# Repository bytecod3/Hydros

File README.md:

### Introduction
Hydros

### Enabling floating point on MicroChip Studio 7
Refer to this article:
https://startingelectronics.org/articles/atmel-AVR-8-bit/print-float-atmel-studio-7/

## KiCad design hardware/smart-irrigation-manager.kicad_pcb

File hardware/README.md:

# smart-irrigation-manager

## Getting started

To make it easy for you to get started with GitLab, here's a list of recommended next steps.

Already a pro? Just edit this README.md and make it your own. Want to make it easy? [Use the template at the bottom](#editing-this-readme)!

## Add your files

- [ ] [Create](https://docs.gitlab.com/ee/user/project/repository/web_editor.html#create-a-file) or [upload](https://docs.gitlab.com/ee/user/project/repository/web_editor.html#upload-a-file) files
- [ ] [Add files using the command line](https://docs.gitlab.com/topics/git/add_files/#add-files-to-a-git-repository) or push an existing Git repository with the following command:

```
cd existing_repo
git remote add origin https://gitlab.com/edwin-mwiti-group/smart-irrigation-manager.git
git branch -M main
git push -uf origin main
```

## Integrate with your tools

- [ ] [Set up project integrations](https://gitlab.com/edwin-mwiti-group/smart-irrigation-manager/-/settings/integrations)

## Collaborate with your team

- [ ] [Invite team members and collaborators](https://docs.gitlab.com/ee/user/project/members/)
- [ ] [Create a new merge request](https://docs.gitlab.com/ee/user/project/merge_requests/creating_merge_requests.html)
- [ ] [Automatically close issues from merge requests](https://docs.gitlab.com/ee/user/project/issues/managing_issues.html#closing-issues-automatically)
- [ ] [Enable merge request approvals](https://docs.gitlab.com/ee/user/project/merge_requests/approvals/)
- [ ] [Set auto-merge](https://docs.gitlab.com/user/project/merge_requests/auto_merge/)

## Test and Deploy

Use the built-in continuous integration in GitLab.

- [ ] [Get started with GitLab CI/CD](https://docs.gitlab.com/ee/ci/quick_start/)
- [ ] [Analyze your code for known vulnerabilities with Static Application Security Testing (SAST)](https://docs.gitlab.com/ee/user/application_security/sast/)
- [ ] [Deploy to Kubernetes, Amazon EC2, or Amazon ECS using Auto Deploy](https://docs.gitlab.com/ee/topics/autodevops/requirements.html)
- [ ] [Use pull-based deployments for improved Kubernetes management](https://docs.gitlab.com/ee/user/clusters/agent/)
- [ ] [Set up protected environments](https://docs.gitlab.com/ee/ci/environments/protected_environments.html)

***

# Editing this README

When you're ready to make this README your own, just edit this file and use the handy template below (or feel free to structure it however you want - this is just a starting point!). Thanks to [makeareadme.com](https://www.makeareadme.com/) for this template.

## Suggestions for a good README

Every project is different, so consider which of these sections apply to yours. The sections used in the template are suggestions for most open source projects. Also keep in mind that while a README can be too long and detailed, too long is better than too short. If you think your README is too long, consider utilizing another form of documentation rather than cutting out information.

## Name
Choose a self-explaining name for your project.

## Description
Let people know what your project can do specifically. Provide context and add a link to any reference visitors might be unfamiliar with. A list of Features or a Background subsection can also be added here. If there are alternatives to your project, this is a good place to list differentiating factors.

## Badges
On some READMEs, you may see small images that convey metadata, such as whether or not all the tests are passing for the project. You can use Shields to add some to your README. Many services also have instructions for adding a badge.

## Visuals
Depending on what you are making, it can be a good idea to include screenshots or even a video (you'll frequently see GIFs rather than actual videos). Tools like ttygif can help, but check out Asciinema for a more sophisticated method.

## Installation
Within a particular ecosystem, there may be a common way of installing things, such as using Yarn, NuGet, or Homebrew. However, consider the possibility that whoever is reading your README is a novice and would like more guidance. Listing specific steps helps remove ambiguity and gets people to using your project as quickly as possible. If it only runs in a specific context like a particular programming language version or operating system or has dependencies that have to be installed manually, also add a Requirements subsection.

## Usage
Use examples liberally, and show the expected output if you can. It's helpful to have inline the smallest example of usage that you can demonstrate, while providing links to more sophisticated examples if they are too long to reasonably include in the README.

## Support
Tell people where they can go to for help. It can be any combination of an issue tracker, a chat room, an email address, etc.

## Roadmap
If you have ideas for releases in the future, it is a good idea to list them in the README.

## Contributing
State if you are open to contributions and what your requirements are for accepting them.

For people who want to make changes to your project, it's helpful to have some documentation on how to get started. Perhaps there is a script that they should run or some environment variables that they need to set. Make these steps explicit. These instructions could also be useful to your future self.

You can also document commands to lint the code or run tests. These steps help to ensure high code quality and reduce the likelihood that the changes inadvertently break something. Having instructions for running tests is especially helpful if it requires external setup, such as starting a Selenium server for testing in a browser.

## Authors and acknowledgment
Show your appreciation to those who have contributed to the project.

## License
For open source projects, say how it is licensed.

## Project status
If you have run out of energy or time for your project, put a note at the top of the README saying that development has slowed down or stopped completely. Someone may choose to fork your project or volunteer to step in as a maintainer or owner, allowing your project to keep going. You can also make an explicit request for maintainers.

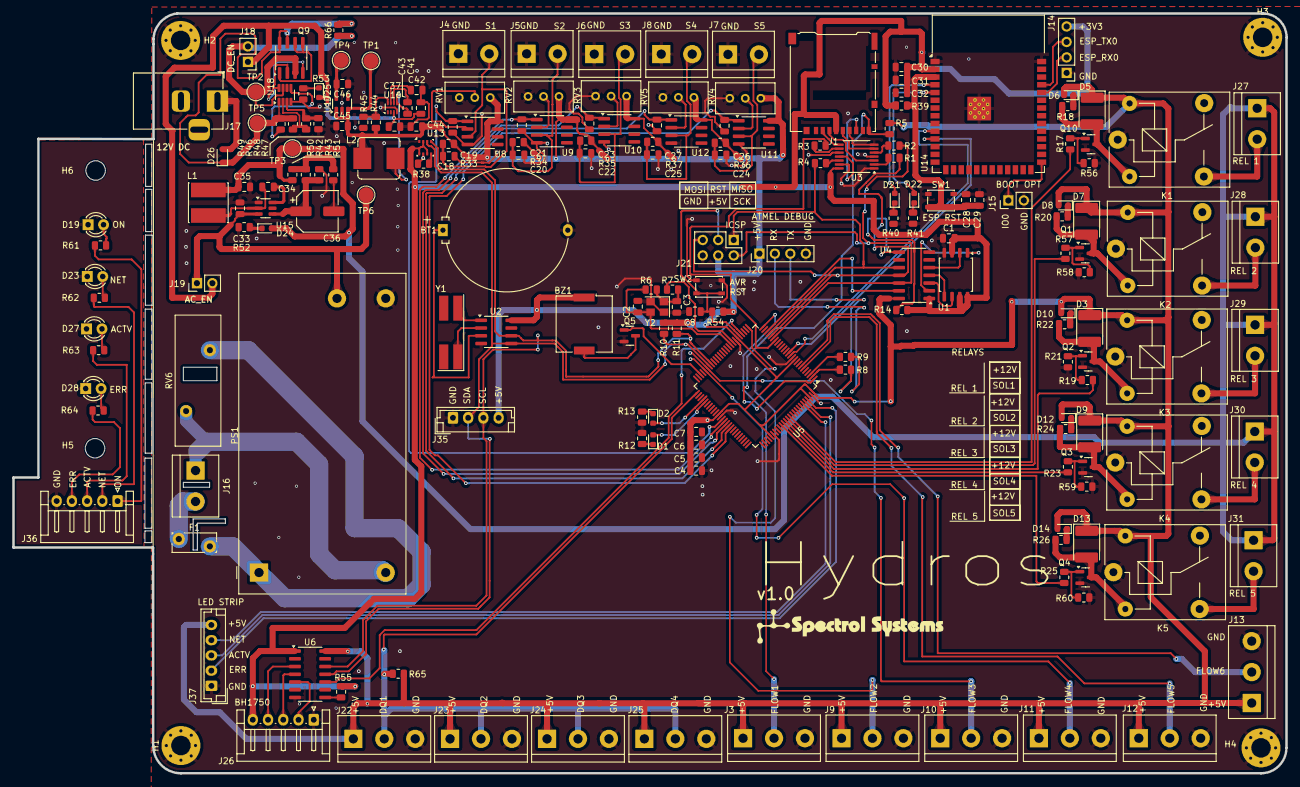
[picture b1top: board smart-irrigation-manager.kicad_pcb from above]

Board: 2 copper layers, 209.0 x 124.7 mm, 203 parts (0 on the bottom side), 142 nets.

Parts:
BT1: 3V Coin Cell - CR2032; Battery_Panasonic_CR2032-HFN_Horizontal_CircularHoles
BZ1: Buzzer; Buzzer_Murata_PKMCS0909E
C1, C4, C5, C6, C7, C8, C18, C19, C20, C21, C22, C23, C24, C25, C26, C27, C28, C30, C34, C37, C43: 100nF; C_0805_2012Metric
C2, C3: 15pF; C_0805_2012Metric
C29, C32: 1uF; C_0805_2012Metric
C31: 22uF; C_0805_2012Metric
C33: 2.22uF; C_0805_2012Metric
C35: 44uF/47uF; C_0805_2012Metric
C36: 100uF; CP_Elec_6.3x5.7
C41: 10uF; C_0805_2012Metric
C42: 33nF; C_0805_2012Metric
C44, C45, C46: 47uF; C_0805_2012Metric
D1, D2, D6, D8, D10, D12, D14, D21, D22, D25: LED; LED_0603_1608Metric
D3, D5, D7, D9, D13: 1N4007; D_2114_3652Metric
D19: RED LED - ON; LED_D3.0mm
D23: GREEN LED - NET; LED_D3.0mm
D24: RED; LED_0603_1608Metric
D26: BAT54J; D_SOD-323F
D27: YELLOW LED -OPER; LED_D3.0mm
D28: RED LED - ERR; LED_D3.0mm
F1: 5A/Resetable(PPTC) - RUEF300; Fuse_Bourns_MF-RG300
H1, H2, H3, H4: MountingHole_Pad; MountingHole_3.2mm_M3_Pad_Via
H5, H6: MountingHole; MountingHole_3.2mm_M3
J1: Micro_SD_Card_Det1; microSD_HC_Hirose_DM3AT-SF-PEJM5
J3, J9, J10, J11, J12, J13: Flow Meter; TerminalBlock_bornier-3_P5.08mm
J4: Soil Moisture Sensor 1; TerminalBlock_bornier-2_P5.08mm
J5: Soil Moisture Sensor 2; TerminalBlock_bornier-2_P5.08mm
J6: Soil Moisture Sensor 3; TerminalBlock_bornier-2_P5.08mm
J7: Soil Moisture Sensor 5; TerminalBlock_bornier-2_P5.08mm
J8: Soil Moisture Sensor 4; TerminalBlock_bornier-2_P5.08mm
J14: ESP-PROG; PinHeader_1x04_P2.54mm_Vertical
J15: BOOT-OPTION; PinHeader_1x02_P2.54mm_Vertical
J16: AC IN; TerminalBlock_bornier-2_P5.08mm
J17: Jack-DC; BarrelJack_Horizontal
J18: DC_EN; PinHeader_1x02_P2.54mm_Vertical
J19: AC_EN; PinHeader_1x02_P2.54mm_Vertical
J20: FTDI_PROGRAMMER; PinHeader_1x04_P2.54mm_Vertical
J21: ICSP; PinHeader_2x03_P2.54mm_Vertical
J22: DS18B20_1; TerminalBlock_bornier-3_P5.08mm
J23: DS18B20_2; TerminalBlock_bornier-3_P5.08mm
J24: DS18B20_3; TerminalBlock_bornier-3_P5.08mm
J25: DS18B20_4; TerminalBlock_bornier-3_P5.08mm
J26: BH1750 LIGHT; JST_EH_S5B-EH_1x05_P2.50mm_Horizontal
J27: REL1_TERMINAL; TerminalBlock_bornier-2_P5.08mm
J28: REL2_TERMINAL; TerminalBlock_bornier-2_P5.08mm
J29: REL3_TERMINAL; TerminalBlock_bornier-2_P5.08mm
J30: REL4_TERMINAL; TerminalBlock_bornier-2_P5.08mm
J31: REL5_TERMINAL; TerminalBlock_bornier-2_P5.08mm
J35: 20x4 LCD connector; JST_EH_B4B-EH-A_1x04_P2.50mm_Vertical
J36: LED_UI_CONNECTOR; JST_EH_S5B-EH_1x05_P2.50mm_Horizontal
J37: LED_UI_CONNECTOR; JST_EH_B5B-EH-A_1x05_P2.50mm_Vertical
K1, K2, K3, K4, K5: SANYOU_SRD_Form_C; Relay_SPDT_SANYOU_SRD_Series_Form_C
L1: 22uH; L_Cenker_CKCS6020
L2: 10uH; L_Bourns_SRP7028A_7.3x6.6mm
PS1: IRM-20-24; Converter_ACDC_MeanWell_IRM-20-xx_THT
Q1, Q2, Q3, Q4, Q10: AO3400A; SOT-23
Q5: BC846; SOT-23
Q9: Si4532DY; SOIC-8_3.9x4.9mm_P1.27mm
R1, R2, R3, R4: 3.3K; R_0805_2012Metric
R5, R21, R33, R34, R35, R36, R37, R38, R56, R58, R59, R60: 10K; R_0805_2012Metric
R6: 1M; R_0805_2012Metric
R7: 27R; R_0805_2012Metric
R8, R9: 22R; R_0805_2012Metric
R10, R11, R14, R54, R55, R65: 4.7k; R_0805_2012Metric
R12, R13, R18, R20, R22, R24, R26: R_500_0805; R_0805_2012Metric
R17, R19, R23, R25, R52, R53, R57: 500R; R_0805_2012Metric
R39, R45: 10K_0805; R_0805_2012Metric
R40, R41: 500R_0805; R_0805_2012Metric
R42: 100K_0805; R_0805_2012Metric
R43: 5.23K_0805; R_0805_2012Metric
R44: 52.3K_0805; R_0805_2012Metric
R46: 243K; R_0805_2012Metric
R47: 59K; R_0805_2012Metric
R48: 1820K; R_0805_2012Metric
R49: 510K_0805; R_0805_2012Metric
R50: 49.9R_0805; R_0805_2012Metric
R51: 2K_0805; R_0805_2012Metric
R61, R62, R63, R64: 270R; R_0805_2012Metric
R66: 0R; R_0805_2012Metric
RV1, RV2, RV3, RV4, RV5: 100K; Potentiometer_Bourns_3296W_Vertical
RV6: 14D471K; RV_Disc_D21.5mm_W7.5mm_P10mm
SW1: RESET; SW_SPST_PTS810
SW2: ATMEL_RST; SW_SPST_PTS810
TP1: 5V_TP; TestPoint_Pad_D2.5mm
TP2: 12V_TP; TestPoint_Pad_D2.5mm
TP3: 12V_AC_TP; TestPoint_Pad_D2.5mm
TP4: 3V3_TP; TestPoint_Pad_D2.5mm
TP5: 12V_DC_TP; TestPoint_Pad_D2.5mm
TP6: 24V_AC_TP; TestPoint_Pad_D2.5mm
U1: W25Q32JVSS; SOIC-8_5.23x5.23mm_P1.27mm
U2: DS1307Z+; SOIC-8_3.9x4.9mm_P1.27mm
U3: 74LVC125; TSSOP-14_4.4x5mm_P0.65mm
U4, U6: TXB0104D; SOIC-14_3.9x8.7mm_P1.27mm
U5: ATmega2560-16A; TQFP-100_14x14mm_P0.5mm
U8, U9, U10, U11, U12: LM393; SOIC-8_3.9x4.9mm_P1.27mm
U13: BME280; Bosch_LGA-8_2.5x2.5mm_P0.65mm_ClockwisePinNumbering
U14: ESP32-S3-WROOM-1
U15: TPS54308; SOT-23-6
U16: TPS62932; SOT-583-8
U17: TLV75533PDBV; SOT-23-5
U18: LTC4365TS8; TSOT-23-8
Y1: 32.768kHz; Crystal_SMD_SeikoEpson_MC406-4Pin_9.6x4.1mm
Y2: 16MHz; Crystal_SMD_3225-4Pin_3.2x2.5mm

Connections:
+3.3V: C46.2, TP4.1, U17.5 (OUT)
+3V3: C1.2, C30.2, C31.2, C32.2, J1.4 (VDD), J14.4, J26.5, R14.2, R39.1, R55.2, U1.3 (IO2), U1.7 (IO3), U1.8 (VCC), U3.14 (VCC), U4.1 (VCCA), U6.1 (VCCA), U13.2 (CSB), U13.6 (VDDIO), U13.8 (VDD), U14.2 (3V3)
+5V: BZ1.1 (+), C4.2, C5.2, C6.2, C7.2, C44.2, C45.2, D3.1 (K), D5.1 (K), D6.2 (A), D7.1 (K), D8.2 (A), D9.1 (K), D10.2 (A), D12.2 (A), D13.1 (K), D14.2 (A), J3.1, J9.1, J10.1, J11.1, J12.1, J13.1, J20.1, J21.4, J22.1, J23.1, J24.1, J25.1, J35.4, J37.5, K1.5, K2.5, K3.5, K4.5, K5.5, L2.2, R5.2, R10.2, R11.2, R33.2, R34.2, R35.2, R36.2, R37.2, R44.1, R54.2, R65.2, RV1.1, RV2.1, RV3.1, RV4.1, RV5.1, TP1.1, U2.8 (VCC), U4.14 (VCCB), U5.10 (VCC), U5.31 (VCC), U5.61 (VCC), U5.80 (VCC), U5.98 (AREF), U5.100 (AVCC), U6.14 (VCCB), U8.8 (V+), U9.8 (V+), U10.8 (V+), U11.8 (V+), U12.8 (V+), U17.1 (IN), U17.3 (EN)
+12V: C35.2, D24.2 (A), J27.1, J28.1, J29.1, J30.1, J31.1, L1.2, R50.1, TP3.1
+24V: C33.1, J19.1, PS1.4 (+Vo), TP6.1, U15.3 (VIN)
/Master/CPU_SECTION/BUZZER: Q5.1 (B), U5.48 (PD5)
/Master/CPU_SECTION/FTDI_RX: J20.2, R9.2
/Master/CPU_SECTION/FTDI_TX: J20.3, R8.2
/Master/CPU_SECTION/F_CLK: U1.6 (CLK), U4.3 (A2)
/Master/CPU_SECTION/F_CS: U1.1 (~CS), U4.2 (A1)
/Master/CPU_SECTION/F_MISO: U1.2 (DO(IO1)), U4.5 (A4)
/Master/CPU_SECTION/F_MOSI: U1.5 (DI(IO0)), U4.4 (A3)
/Master/CPU_SECTION/RXD0: R8.1, U5.2 (PE0)
/Master/CPU_SECTION/SD_CLK: J1.5 (CLK), U3.6
/Master/CPU_SECTION/SD_CS: J1.2 (DAT3/CD), U3.8
/Master/CPU_SECTION/SD_MISO: J1.7 (DAT0), U3.11
/Master/CPU_SECTION/SD_MOSI: J1.3 (CMD), U3.3
/Master/CPU_SECTION/TXD0: R9.1, U5.3 (PE1)
/Master/CPU_SECTION/USER_LED1: D2.2 (A), U5.54 (PC1)
/Master/CPU_SECTION/USER_LED2: D1.2 (A), U5.55 (PC2)
/Master/OUTPUT_CONTROL/REL1_PULSE: D5.2 (A), K1.2, Q10.3 (D), R18.1
/Master/OUTPUT_CONTROL/REL2_PULSE: D7.2 (A), K2.2, Q1.3 (D), R20.1
/Master/OUTPUT_CONTROL/REL3_PULSE: D3.2 (A), K3.2, Q2.3 (D), R22.1
/Master/OUTPUT_CONTROL/REL4_PULSE: D9.2 (A), K4.2, Q3.3 (D), R24.1
/Master/OUTPUT_CONTROL/REL5_PULSE: D13.2 (A), K5.2, Q4.3 (D), R26.1
/Master/POWER SUPPLY UNIT/12V_DC: J18.2, Q9.3 (1), R66.1, TP2.1, U18.7 (Vout)
/Master/POWER SUPPLY UNIT/AC_IN: F1.2, PS1.1 (AC/L), RV6.1
/Master/POWER SUPPLY UNIT/L_IN: F1.1, J16.2
/Master/POWER SUPPLY UNIT/N_IN: J16.1, PS1.2 (AC/N), RV6.2
/Master/SENSORS AND INPUTS/LIGHT_ADDR: J26.2, U6.5 (A4)
/Master/SENSORS AND INPUTS/LIGHT_SCL: J26.4, U6.3 (A2)
/Master/SENSORS AND INPUTS/LIGHT_SDA: J26.3, U6.4 (A3)
/Master/WIFI AND COMMS/ESP_EN: C28.2, C29.2, R39.2, SW1.2, U14.3 (EN)
/Master/WIFI AND COMMS/ESP_RX0: J14.2, U14.36 (RXD0)
/Master/WIFI AND COMMS/ESP_TX0: J14.3, U14.37 (TXD0)
/Master/WIFI AND COMMS/USER_LED1: D21.2 (A), U14.4 (IO4)
/Master/WIFI AND COMMS/USER_LED2: D22.2 (A), U14.5 (IO5)
BH1750_ADDR: U5.29 (PG4), U6.10 (B4)
ESP_RX1: U5.13 (PH1), U14.11 (IO18)
ESP_TX1: U5.12 (PH0), U14.10 (IO17)
FLOW_METER_1: J3.2, U5.25 (PB6)
FLOW_METER_2: J9.2, U5.26 (PB7)
FLOW_METER_3: J10.2, U5.45 (PD2)
FLOW_METER_4: J11.2, U5.46 (PD3)
FLOW_METER_5: J12.2, U5.6 (PE4)
FLOW_METER_6: J13.2, U5.7 (PE5)
GND: BT1.2 (-), C1.1, C2.1, C3.1, C4.1, C5.1, C6.1, C7.1, C8.1, C18.2, C19.2, C20.2, C21.2, C22.2, C23.2, C24.2, C25.2, C26.2, C27.2, C28.1, C29.1, C30.1, C31.1, C32.1, C33.2, C35.1, C37.2, C41.2, C42.2, C44.1, C45.1, C46.1, H1.1, H2.1, H3.1, H4.1, J1.6 (VSS), J3.3, J4.1, J5.1, J6.1, J7.1, J8.1, J9.3, J10.3, J11.3, J12.3, J13.3, J14.1, J15.2, J17.2, J20.4, J21.6, J22.3, J23.3, J24.3, J25.3, J26.1, J35.1, J37.1, K1.1, K2.1, K3.1, K4.1, K5.1, PS1.3 (-Vo), Q1.2 (S), Q2.2 (S), Q3.2 (S), Q4.2 (S), Q5.2 (E), Q10.2 (S), R12.1, R13.1, R21.1, R38.2, R40.1, R41.1, R43.2, R45.2, R47.2, R52.2, R53.2, R56.1, R58.1, R59.1, R60.1, RV1.3, RV2.3, RV3.3, RV4.3, RV5.3, SW1.1, SW2.1, U1.4 (GND), U2.4 (GND), U3.1, U3.4, U3.7 (GND), U3.10, U3.13, U4.7 (GND), U5.11 (GND), U5.32 (GND), U5.62 (GND), U5.81 (GND), U5.99 (GND), U6.7 (GND), U8.4 (V-), U9.4 (V-), U10.4 (V-), U11.4 (V-), U12.4 (V-), U13.1 (GND), U13.7 (GND), U14.1 (GND), U14.40 (GND), U14.41 (GND), U15.1 (GND), U16.4 (GND), U17.2 (GND), U18.4 (GND), Y2.2, Y2.4
GREEN_NET: J37.4, U5.95 (PF2)
MCU_FLASH_CS: U4.13 (B1), U5.23 (PB4)
MCU_SD_CS: R3.1, U5.19 (PB0)
unnamed: BT1.1 (+), U2.3 (VBAT)
unnamed: BZ1.2 (-), Q5.3 (C)
unnamed: C3.2, R6.2, R7.1, Y2.1
unnamed: C36.2, R51.1
unnamed: D1.1 (K), R12.2
unnamed: D2.1 (K), R13.2
unnamed: D6.1 (K), R18.2
unnamed: D8.1 (K), R20.2
unnamed: D10.1 (K), R22.2
unnamed: D12.1 (K), R24.2
unnamed: D14.1 (K), R26.2
unnamed: D19.2 (A), R61.2
unnamed: D19.1 (K), D23.1 (K), D27.1 (K), D28.1 (K), J36.5
unnamed: D21.1 (K), R40.2
unnamed: D22.1 (K), R41.2
unnamed: D23.2 (A), R62.2
unnamed: D24.1 (K), R52.1
unnamed: C37.1, C41.1, D25.2 (A), J18.1, J19.2, U16.3 (VIN)
unnamed: D25.1 (K), R53.1
unnamed: D26.2 (A), J17.1
unnamed: D26.1 (K), Q9.7 (D), Q9.8 (D), R48.1, R49.1, R66.2, TP5.1, U18.1 (Vin)
unnamed: D27.2 (A), R63.2
unnamed: D28.2 (A), R64.2
unnamed: C18.1, J4.2, R33.1, U8.3 (+)
unnamed: C20.1, J5.2, R34.1, U9.3 (+)
unnamed: C22.1, J6.2, R35.1, U10.3 (+)
unnamed: C24.1, J7.2, R36.1, U11.3 (+)
unnamed: C25.1, J8.2, R37.1, U12.3 (+)
unnamed: J15.1, U14.27 (IO0)
unnamed: J27.2, K1.3
unnamed: J28.2, K2.3
unnamed: J29.2, K3.3
unnamed: J30.2, K4.3
unnamed: J31.2, K5.3
unnamed: J36.1, R61.1
unnamed: J36.2, R62.1
unnamed: J36.3, R63.1
unnamed: J36.4, R64.1
unnamed: Q1.1 (G), R57.2, R58.2
unnamed: Q2.1 (G), R19.2, R21.2
unnamed: Q3.1 (G), R23.2, R59.2
unnamed: Q4.1 (G), R25.2, R60.2
unnamed: Q9.2 (G), Q9.4 (G), U18.8 (GATE)
unnamed: Q9.1 (S), Q9.5 (D), Q9.6 (D)
unnamed: Q10.1 (G), R17.2, R56.2
unnamed: R1.2, U3.2
unnamed: R2.2, U3.5
unnamed: R3.2, U3.9
unnamed: R4.2, U3.12
unnamed: R42.1, R50.2, R51.2
unnamed: U2.1 (X1), Y1.2
unnamed: U2.2 (X2), Y1.1
unnamed: R14.1, U4.8 (OE)
unnamed: C2.2, R6.1, U5.34 (XTAL1), Y2.3
unnamed: R7.2, U5.33 (XTAL2)
unnamed: R55.1, U6.8 (OE)
unnamed: RV1.2, U8.2 (-)
unnamed: RV2.2, U9.2 (-)
unnamed: RV3.2, U10.2 (-)
unnamed: RV4.2, U11.2 (-)
unnamed: RV5.2, U12.2 (-)
unnamed: R38.1, U13.5 (SDO)
unnamed: C34.1, U15.6 (BOOT)
unnamed: C36.1, R42.2, R43.1, U15.4 (FB)
unnamed: C34.2, L1.1, U15.2 (SW)
unnamed: C43.1, U16.6 (BST)
unnamed: R44.2, R45.1, U16.8 (FB)
unnamed: C42.1, U16.7 (SS)
unnamed: C43.2, L2.1, U16.5 (SW)
unnamed: R46.2, R47.1, U18.3 (OV)
unnamed: R46.1, R48.2, U18.2 (UV)
unnamed: R49.2, U18.5 (~SHDN)
RED_ERR: J37.2, U5.97 (PF0)
REL1_SIG: R17.1, U5.89 (PK0)
REL2_SIG: R57.1, U5.88 (PK1)
REL3_SIG: R19.1, U5.87 (PK2)
REL4_SIG: R23.1, U5.86 (PK3)
REL5_SIG: R25.1, U5.85 (PK4)
RESET: C8.2, J21.3, R54.1, SW2.2, U5.30 (~RESET)
SCL: J35.3, R11.1, U2.6 (SCL), U5.43 (PD0), U6.12 (B2), U13.4 (SCK)
SDA: J35.2, R10.1, U2.5 (SDA), U5.44 (PD1), U6.11 (B3), U13.3 (SDI)
SD_DETECT: J1.9 (DET), R5.1, U5.1 (PG5)
SOIL_SIG1: C19.1, U5.63 (PJ0), U8.1
SOIL_SIG2: C21.1, U5.64 (PJ1), U9.1
SOIL_SIG3: C23.1, U5.65 (PJ2), U10.1
SOIL_SIG4: C27.1, U5.66 (PJ3), U12.1
SOIL_SIG5: C26.1, U5.67 (PJ4), U11.1
SPI_MISO: J21.1, R4.1, U4.10 (B4), U5.22 (PB3)
SPI_MOSI: J21.5, R1.1, U4.11 (B3), U5.21 (PB2)
SPI_SCK: J21.2, R2.1, U4.12 (B2), U5.20 (PB1)
TEMP: J22.2, J23.2, J24.2, J25.2, R65.1, U5.51 (PG0)
YELLOW_OPER: J37.3, U5.96 (PF1)

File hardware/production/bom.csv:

Designator,Footprint,Quantity,Value,LCSC Part #
BT1,Battery_Panasonic_CR2032-HFN_Horizontal_CircularHoles,1,3V Coin Cell - CR2032,
BZ1,Buzzer_Murata_PKMCS0909E,1,Buzzer,
"C1, C18, C19, C20, C21, C22, C23, C24, C25, C26, C27, C28, C30, C34, C37, C4, C43, C5, C6, C7, C8",0805,21,100nF,
"C2, C3",0805,2,15pF,
"C29, C32",0805,2,1uF,
C31,0805,1,22uF,
C33,0805,1,2.22uF,
C35,0805,1,44uF/47uF,
C36,CP_Elec_6.3x5.7,1,100uF,
C41,0805,1,10uF,
C42,0805,1,33nF,
"C44, C45, C46",0805,3,47uF,
"D1, D10, D12, D14, D2, D21, D22, D25, D6, D8",0603,10,LED,
"D13, D3, D5, D7, D9",2114,5,1N4007,
D19,LED_D3.0mm,1,RED LED - ON,
D23,LED_D3.0mm,1,GREEN LED - NET,
D24,0603,1,RED,
D26,D_SOD-323F,1,BAT54J,
D27,LED_D3.0mm,1,YELLOW LED -OPER,
D28,LED_D3.0mm,1,RED LED - ERR,
F1,Fuse_Bourns_MF-RG300,1,5A/Resetable(PPTC) - RUEF300,
J1,microSD_HC_Hirose_DM3AT-SF-PEJM5,1,Micro_SD_Card_Det1,
"J10, J11, J12, J13, J3, J9",TerminalBlock_bornier-3_P5.08mm,6,Flow Meter,
J14,PinHeader_1x04_P2.54mm_Vertical,1,ESP-PROG,
J15,PinHeader_1x02_P2.54mm_Vertical,1,BOOT-OPTION,
J16,TerminalBlock_bornier-2_P5.08mm,1,AC IN,
J17,BarrelJack_Horizontal,1,Jack-DC,
J18,PinHeader_1x02_P2.54mm_Vertical,1,DC_EN,
J19,PinHeader_1x02_P2.54mm_Vertical,1,AC_EN,
J20,PinHeader_1x04_P2.54mm_Vertical,1,FTDI_PROGRAMMER,
J21,PinHeader_2x03_P2.54mm_Vertical,1,ICSP,
J22,TerminalBlock_bornier-3_P5.08mm,1,DS18B20_1,
J23,TerminalBlock_bornier-3_P5.08mm,1,DS18B20_2,
J24,TerminalBlock_bornier-3_P5.08mm,1,DS18B20_3,
J25,TerminalBlock_bornier-3_P5.08mm,1,DS18B20_4,
J26,JST_EH_S5B-EH_1x05_P2.50mm_Horizontal,1,BH1750 LIGHT,
J27,TerminalBlock_bornier-2_P5.08mm,1,REL1_TERMINAL,
J28,TerminalBlock_bornier-2_P5.08mm,1,REL2_TERMINAL,
J29,TerminalBlock_bornier-2_P5.08mm,1,REL3_TERMINAL,
J30,TerminalBlock_bornier-2_P5.08mm,1,REL4_TERMINAL,
J31,TerminalBlock_bornier-2_P5.08mm,1,REL5_TERMINAL,
J35,JST_EH_B4B-EH-A_1x04_P2.50mm_Vertical,1,20x4 LCD connector,
J36,JST_EH_S5B-EH_1x05_P2.50mm_Horizontal,1,LED_UI_CONNECTOR,
J37,JST_EH_B5B-EH-A_1x05_P2.50mm_Vertical,1,LED_UI_CONNECTOR,
J4,TerminalBlock_bornier-2_P5.08mm,1,Soil Moisture Sensor 1,
J5,TerminalBlock_bornier-2_P5.08mm,1,Soil Moisture Sensor 2,
J6,TerminalBlock_bornier-2_P5.08mm,1,Soil Moisture Sensor 3,
J7,TerminalBlock_bornier-2_P5.08mm,1,Soil Moisture Sensor 5,
J8,TerminalBlock_bornier-2_P5.08mm,1,Soil Moisture Sensor 4,
"K1, K2, K3, K4, K5",Relay_SPDT_SANYOU_SRD_Series_Form_C,5,SANYOU_SRD_Form_C,
L1,L_Cenker_CKCS6020,1,22uH,
L2,L_Bourns_SRP7028A_7.3x6.6mm,1,10uH,
PS1,Converter_ACDC_MeanWell_IRM-20-xx_THT,1,IRM-20-24,
"Q1, Q10, Q2, Q3, Q4",SOT-23,5,AO3400A,
Q5,SOT-23,1,BC846,
"R1, R2, R3, R4",0805,4,3.3K,
"R10, R11, R14, R54, R55, R65",0805,6,4.7k,
"R12, R13, R18, R20, R22, R24, R26",0805,7,R_500_0805,
"R17, R19, R23, R25, R52, R53, R57",0805,7,500R,
"R21, R33, R34, R35, R36, R37, R38, R5, R56, R58, R59, R60",0805,12,10K,
"R39, R45",0805,2,10K_0805,
"R40, R41",0805,2,500R_0805,
R42,0805,1,100K_0805,
R43,0805,1,5.23K_0805,
R44,0805,1,52.3K_0805,
R50,0805,1,49.9R_0805,
R51,0805,1,2K_0805,
R6,0805,1,1M,
"R61, R62, R63, R64",0805,4,270R,
R66,0805,1,0R,
R7,0805,1,27R,
"R8, R9",0805,2,22R,
"RV1, RV2, RV3, RV4, RV5",Potentiometer_Bourns_3296W_Vertical,5,100K,
RV6,RV_Disc_D21.5mm_W7.5mm_P10mm,1,14D471K,
SW1,SW_SPST_PTS810,1,RESET,
SW2,SW_SPST_PTS810,1,ATMEL_RST,
TP1,TestPoint_Pad_D2.5mm,1,5V_TP,
TP2,TestPoint_Pad_D2.5mm,1,12V_TP,
TP3,TestPoint_Pad_D2.5mm,1,12V_AC_TP,
TP4,TestPoint_Pad_D2.5mm,1,3V3_TP,
TP5,TestPoint_Pad_D2.5mm,1,12V_DC_TP,
TP6,TestPoint_Pad_D2.5mm,1,24V_AC_TP,
U1,SOIC-8_5.23x5.23mm_P1.27mm,1,W25Q32JVSS,
"U10, U11, U12, U8, U9",SOIC-8_3.9x4.9mm_P1.27mm,5,LM393,
U13,Bosch_LGA-8_2.5x2.5mm_P0.65mm_ClockwisePinNumbering,1,BME280,
U14,ESP32-S3-WROOM-1,1,ESP32-S3-WROOM-1,
U15,SOT-23-6,1,TPS54308,
U16,SOT-583-8,1,TPS62932,
U17,SOT-23-5,1,TLV75533PDBV,
U2,SOIC-8_3.9x4.9mm_P1.27mm,1,DS1307Z+,
U3,TSSOP-14_4.4x5mm_P0.65mm,1,74LVC125,
"U4, U6",SOIC-14_3.9x8.7mm_P1.27mm,2,TXB0104D,
U5,TQFP-100_14x14mm_P0.5mm,1,ATmega2560-16A,
Y1,Crystal_SMD_SeikoEpson_MC406-4Pin_9.6x4.1mm,1,32.768kHz,
Y2,Crystal_SMD_3225-4Pin_3.2x2.5mm,1,16MHz,

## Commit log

2025-06-11 ADDS non-blocking delay
2025-06-12 ADDS blocking 1sec delay
2025-06-12 ADDS CTC timer
2025-06-14 ADDS flow meter calculation
2025-06-17 adds ds18b20 defs
2025-06-17 ADDS temp sensor code
2025-06-19 ADDS production files
2025-07-08 ADDS working DS18B20 lib
2025-08-07 ADDS relay control hdroswitch
2025-08-07 ADDS LORA initializer :tada:
